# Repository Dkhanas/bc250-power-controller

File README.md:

# BC-250 power controller

A small board that gives an AMD BC-250 (running SteamOS) a real power button and Bluetooth controller wake-up.
A Raspberry Pi Pico 2 W sits on the ATX power supply's 5 V standby rail and:

- **Case button** short press: PSU on (the BC-250 auto-boots) / clean SteamOS shutdown (USB power key)
- **Case button held 5 s:** force the PSU off
- **Wi-Fi (optional):** a phone page / home-screen icon (`http://bc250.local`): power on, shut down, your controllers
  with battery, pair new ones, forget old ones. **Home Assistant** via MQTT (separate firmware file). Set up from your phone in a minute.
  Wi-Fi runs only when you want it: on request (default), only while the console is off, always, or never
- **Low-battery warning:** the controller rumbles and the button LED blinks when a DualSense / DualShock is at 20 % or less
- **Case button held 8 s (console off):** Wi-Fi on for the phone page
- **Case button held 2 s:** pairing window, which accepts a new controller for 60 s. Outside it, controllers in
  pairing mode are ignored, so you can still pair yours with a phone or PC
- **Bluetooth controller** (DualSense, DS4, Switch Pro, Xbox, 8BitDo…): pressing PS / Xbox / Home wakes the board,
  and the controller is passed to the BC-250 over USB (as itself, or as an Xbox 360 pad)
- **TPM pin 9** of the BC-250 goes low after shutdown -> PSU off after 5 s
- **Button LED:** slow blink booting, solid running, fast blink shutting down
- **Second fan** powered from the PSU's 12 V, speed controlled by the BC-250 (J4003)

| Printed board (PCB v12) | Test board (perfboard) |
|---|---|
|  |  |

## Repository

| Folder | What |
|---|---|
| [`firmware/`](firmware/) | Pico 2 W firmware (C, Pico SDK 2.3.1 + Bluepad32). Ready-to-flash file in [`firmware/release/`](firmware/release/) |
| [`pcb/`](pcb/) | Printed board, v12: KiCad project, Gerbers for JLCPCB / PCBWay / Aisler, notes |
| [`perfboard/`](perfboard/) | Test board on a 70×90 mm perfboard: hole-by-hole map |
| [`.github/workflows/`](.github/workflows/) | Automatic firmware build on GitHub; a version tag (`v8`) publishes a Release with both `.uf2` files |
| [`docs/`](docs/) | Build plan (wiring to the BC-250, SteamOS settings, mounting) and [pin drawings](docs/pinout.md) of every connector |
| [`CHANGELOG.md`](CHANGELOG.md) | Release notes: what's new, fixed and known issues in each firmware and PCB version |
| [`bom.csv`](bom.csv) | Parts list for both boards (opens in Excel; GitHub shows it as a table) |

## Quick start

1. **Flash:** hold BOOTSEL on the Pico, plug it into a PC, copy `firmware/release/bc250_power_v8.uf2` onto the `RP2350` drive
   (or `bc250_power_v8_ha.uf2` if you use Home Assistant).
2. **BC-250:** AUTO_PWRON jumper on pins 1–2; SteamOS `HandlePowerKey=poweroff`.
3. **Wire** per [`docs/build-plan.md`](docs/build-plan.md) (Pico GP15 -> PSU, GP17 <- button, GP16 -> LED, GP2 <- TPM pin 9).
   Pin drawings of every connector (BC-250 J4003 / TPMS1, ATX, board headers, Pico): [`docs/pinout.md`](docs/pinout.md).
4. **Pair a controller:** hold the case button 2 s and release (LED double-blinks), then put the controller in
   pairing mode within 60 s. Pairing turns the BC-250 on if it was off (expected).
5. **Optional Wi-Fi:** console off, hold the case button **8 s** (LED stays lit), release. On your phone tap the
   Wi-Fi **`BC250-setup`**; the setup page opens by itself. Pick your network, type its password, done. Then open
   `http://bc250.local` and *Add to Home Screen*. Wi-Fi switches itself off when unused (Settings → "Wi-Fi is on").

## Downsides and known limitations

**Testing status**
- **Firmware v8 compiles cleanly but hasn't been tested on real hardware yet** (v4 and v5 ran on the real board).
  Its web page was tested in a browser against a simulated Pico.
- **Wi-Fi and Bluetooth share one radio chip.** If controllers lag with Wi-Fi "Always", use "Only while the console
  is off" (Settings). Home Assistant only sees the BC-250 while Wi-Fi is on. Wi-Fi is 2.4 GHz only and adds a little standby power. Until a network is saved (or when it
  stays unreachable), the Pico runs the open setup Wi-Fi `BC250-setup`; someone nearby could set it up first.
  `bc250.local` doesn't open on some Android phones: use the Pico's address from your router. Without a PIN (`pin 1234`), anyone on your
  network can use the web page's buttons.
- **Battery level only for DualSense / DualShock**; Xbox, Switch Pro and 8BitDo don't report it to the Pico.
  Its key guard works around a Bluepad32 behaviour: after one failed reconnect Bluepad32 deletes the controller's
  pairing key, which made controllers "search" forever until re-paired. The Bluetooth repair from v5 stays for
  real radio hangs. The log (`sudo cat /dev/ttyACM0`) shows which one happened.
- **Controllers paired before v6 aren't protected until their first successful connection with v6.** If one
  already lost its key, re-pair it once.
- **Bluetooth repair takes a moment:** when Bluetooth is stuck, the Pico notices within about 30 s and restarts
  only Bluetooth, which takes a few more seconds. Until then, PS doesn't reconnect.
- **The log port only exists while no controller is connected**, so controller identities stay exact.
- **PCB v12 was checked with KiCad DRC, not built yet.** Everything except the ATX header was tested on a built v8 board;
  v12's ATX pin order matches what was measured there with the real PSU cable.
  Check the first board with a multimeter before connecting the PSU (see [`pcb/README.md`](pcb/README.md)).
  Check the first board with a multimeter before connecting the PSU (see [`pcb/README.md`](pcb/README.md)).
- **The perfboard map (v16) has the ATX header mirrored.** Wire it by wire colour, not by the hole numbers.

**Controllers**
- **Whenever a controller joins or leaves, every controller drops for about 0.5 s.** The Pico re-plugs itself on USB
  with the new layout, and Steam may reassign player numbers.
- **Several real DualSense / DS4 / Switch Pro controllers inside one USB device is unusual.** Linux supports it,
  but Steam may show only one of them. Mixed groups fall back to Xbox 360 pads, which lose the touchpad, gyro,
  lightbar and adaptive triggers.
- **No audio:** the DualSense / DS4 headphone jack, speaker and mic aren't passed through.
- **Up to 4 controllers. Only Bluetooth ones work**: no wired controllers through the Pico, and no non-Bluetooth Xbox One pads.
- **New controllers only pair while the pairing window is open** (case button held 2 s). Bluetooth LE controllers
  already bonded to the Pico (e.g. Xbox) are still taken when put in pairing mode, because they reconnect the same way.
- **Pairing a controller turns the BC-250 on.** For 20 s after a shutdown, controllers that reconnect are ignored,
  so a quick press of PS right after power-off does nothing.

**Power and shutdown**
- **The shutdown key is a USB "Power" key.** SteamOS has to be set to `HandlePowerKey=poweroff`. Gaming mode or an
  inhibitor can swallow it; then press again, or hold 5 s.
- **Holding the button for 5 s cuts power hard,** with no clean shutdown, like pulling the plug.
- **A short press while the board is booting is ignored.**
- **"Off" is detected from TPM header pin 9.** If the board doesn't boot within 180 s, the PSU is switched off again.
- **When a controller identity is active, the power key needs a ~2 s USB re-plug first.** The controllers vanish from
  SteamOS at that moment, which doesn't matter because it's shutting down.

**Hardware**
- **The Pico is always powered from the PSU's 5 V standby rail,** with its Bluetooth radio on, so the PC draws a little more
  power while "off".
- **With a normal USB cable, a little standby power can leak into the switched-off BC-250** through the Pico's
  internal diode (its back-panel LEDs may glow faintly). The clean fix is a cable with the red 5 V wire cut, plus
  `USE_VBUS_SENSE 0` in `firmware/src/config.h`.
- **Specific to the BC-250 and an ATX PSU** (needs AUTO_PWRON, the TPM header and J4003). Other boards need new pin mapping and logic.
- **No Wi-Fi features** (no web page or remote power-on over the network).

## ⚠️ Safety notes

- **ATX header orientation:** the two pin rows are **5.5 mm apart** (PCB v1–v8 used 4.2 mm: never use them).
  With the latch facing the wall, **pin 1 is at the FRONT end** (KiCad's official footprint, measured on a built v8 board).
  PCB v10 / v11 had it mirrored (12 V on GND): never use them. Use **PCB v9 or v12**.
- **Pico VBUS (pin 40) stays unconnected** on the board. The USB cable's 5 V (red wire) can leak standby power into a
  switched-off BC-250; firmware v4 and later handle a normal cable (`USE_VBUS_SENSE 1`).

## Versions

| | Version | Date |
|---|---|---|
| Firmware | v8 – Wi-Fi phone page (setup from the phone, controller list, pairing, forget) + Home Assistant, low-battery warning, pairing window, key guard, Bluetooth repair, event log | 2026-11-06 |
| PCB | v12 – v9 ATX pin order (confirmed with the real PSU cable) + gaps between the front headers | 2026-11-06 |
| Perfboard map | v16 (ATX header mirrored – wire it by wire colour) | 2026-10-18 |

**Building:** `bash firmware/build.sh` (library versions pinned in `firmware/deps.env`), or download the `.uf2` from
GitHub (Actions / Releases).

**Release notes for every version:** [`CHANGELOG.md`](CHANGELOG.md). Technical details: [`firmware/README.md`](firmware/README.md), [`pcb/README.md`](pcb/README.md).

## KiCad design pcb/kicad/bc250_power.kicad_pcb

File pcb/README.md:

# Printed board – PCB v12

| | |
|---|---|
| **Top** (component side, rendered from the board file) | **Bottom** (seen from below) |
|  |  |

**Wiring diagram** (colour-coded nets, dashed = top layer):

## Files
| File | What |
|---|---|
| [`gerbers/bc250_power_gerbers_v12.zip`](gerbers/bc250_power_gerbers_v12.zip) | Upload this to the board maker |
| [`kicad/`](kicad/) | KiCad 7+ project (`bc250_power.kicad_pro` / `.kicad_pcb`), `gen_board.py` (generates the board), `check_board.py` (clearance / connectivity check), `render_board.py` (makes the images) |
| [`images/`](images/) | The pictures on this page |

**Never use PCB v1–v8, v10 or v11.** v1–v8: ATX rows 4.2 mm apart (the real header is 5.5 mm), no peg holes.
v10 / v11: ATX pin order mirrored (pin 1 at the back) – 12 V on GND.

- Board 57.5 × 72 mm, 2 layers, 1.6 mm. 4 × M3 holes (3.2 mm); three at 3.5 mm from the corners, the front-right one
  3.0 mm from the right edge and 2.5 mm from the front edge (clears J3).
- Grid: hole (col 6, row 1) at x 6.5, y −1.0 mm; 2.54 mm pitch. Derived from perfboard map v16.

## Ordering
Upload `gerbers/bc250_power_gerbers_v12.zip` to JLCPCB / PCBWay / Aisler: 2 layers, 1.6 mm, defaults for everything else.

## ATX header (Molex Mini-Fit Jr 5566-24A2)
Latch faces the wall, pins 13–24 on the wall side, **pin 1 at the FRONT end, pins 12 / 24 at the back**.
Rows 5.5 mm apart, 3.3 × 2.7 mm oval pads, 1.4 mm drills, two 3.0 mm holes for the snap-in pegs.
Matches KiCad's official footprint pin-for-pin and was **confirmed with the real PSU cable on a built v8 board** (whose own ATX footprint was wrong;
everything else on it worked): 5 V standby is on the
4th pin from the back in the Pico-side row.

| ATX pin | Position (counted from the back / honeycomb wall end) | Goes to |
|---|---|---|
| 9 5VSB (purple) | Pico-side row, 4th | col 18 → D1 anode → Pico VSYS |
| 10 +12V (yellow) | Pico-side row, 3rd | top layer, x 40.8 mm → row 26 → J3 pin 3 |
| 15 GND (black) | wall-side row, 10th (3rd from the front) | lane beside the wall row → J3 pin 4 → row 29 → J1 GND → Pico GND |
| 16 PS_ON (green) | wall-side row, 9th (4th from the front) | channel between the rows → Q1 collector |

All-black modular cables: check with a multimeter (black probe on the PSU case): only the 5VSB pin reads ~5 V while the PSU is off.

## v12 (6 Nov 2026)
- v9's ATX pin order (confirmed with the real PSU cable) with v11's spaced-out front headers.
- Front row (row 27), left to right: J1 button (cols 12–14: LED+, C, GND), gap, J2 TPM9 (col 16), gap,
  J4 → J4003 (cols 18 T, 19 P), gap, J3 fan 2 (cols 21–24: PWM, TACH, 12V, GND).
- Checks: KiCad DRC 0 electrical errors, 0 unconnected pads; independent clearance/connectivity script 0 errors;
  ATX pads compared with the official footprint (0.0 mm error).

## Layout
- Q1 2N2222 flat on row 3 (E col 15, B col 16, C col 17). R1 1k row 5 (col 14 → 17). R2 10k col 16 (row 6 base → row 9 GND).
  v12 moved Q1 and R2 left: ≥ 5.5 mm between them and the ATX connector body (was 0.4 mm).
- R3 220 Ω col 15 (rows 21–24) → J2. D1 1N5819 row 25 (K col 14, A col 18), VSYS row 25 → col 7 → Pico pin 39.
- Pico on cols 6/13 rows 5–24; VBUS (pin 40) unconnected.
- Trace widths: 1.0 mm for GND / 5VSB / VSYS / 12V, 0.4–0.6 mm for signals.

## Before first power-up
Plug the PSU cable in (PSU off): pad 9 must read +5 V to GND, every other ATX pad 0 V.
Then Pico VSYS (2nd pin from the USB end, left row) ≈ 4.7 V and 3V3 (5th pin) = 3.3 V.

## History
- v2–v5 (18 Oct): narrower board, J1 to the front, headers in one row, J2 joins the row.
- v6–v8: layout tweaks. v8 was built: everything worked except the ATX header (4.2 mm rows, mirrored).
- v9 (19 Oct): ATX header corrected (5.5 mm rows, peg holes, pin 1 at the front). Pin order later confirmed with the real PSU cable.
- v10 / v11 (6 Nov): pin 1 at the back + gaps between front headers – **wrong pin order, do not use**.
- v12 (6 Nov): v9 pin order + v11 gaps.

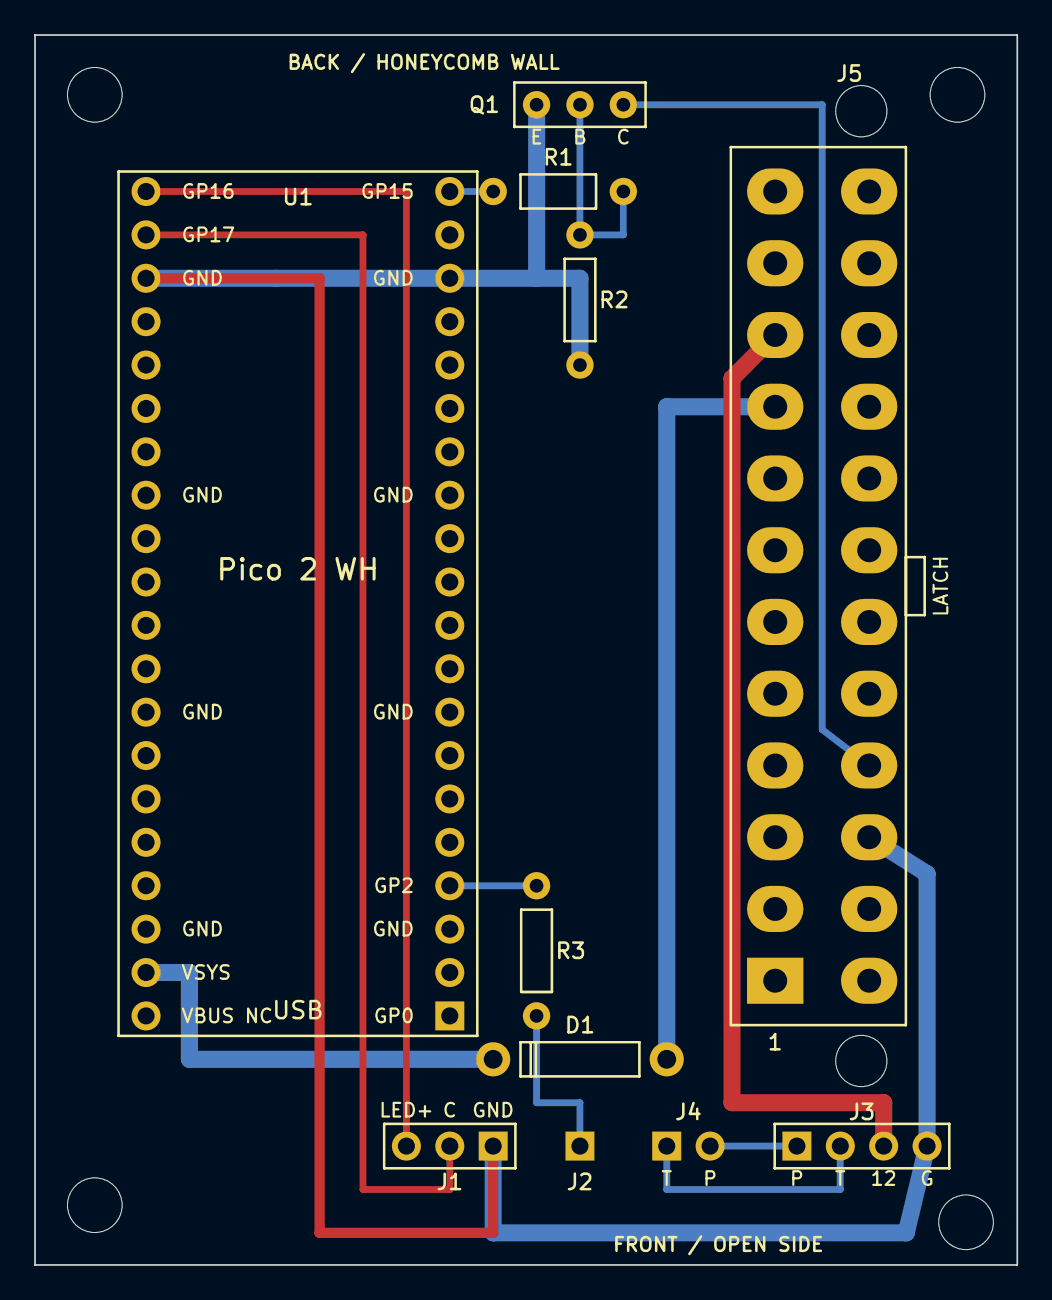
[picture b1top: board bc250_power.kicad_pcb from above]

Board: 2 copper layers, 57.5 x 72.0 mm, 15 parts (0 on the bottom side), 13 nets.

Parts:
D1: 1N5819; D1_1N5819
H1: M3; H1_M3
H2: M3; H2_M3
H3: M3; H3_M3
H4: M3; H4_M3
J1: BUTTON; J1_BUTTON
J2: TPM9; J2_TPM9
J3: FAN2; J3_FAN2
J4: J4003; J4_J4003
J5: ATX24; J5_ATX24
Q1: 2N2222; Q1_2N2222
R1: 1k; R1_1k
R2: 10k; R2_10k
R3: 220R; R3_220R
U1: Pico2WH; U1_Pico2WH

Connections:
5VSB: D1.A, J5.9
+12V: J3.3, J5.10
BTN: J1.2, U1.22
FAN_PWM: J3.1, J4.2
FAN_TACH: J3.2, J4.1
GND: J1.1, J3.4, J5.15, Q1.E, R2.2, U1.18, U1.23
GP2: R3.1, U1.4
GP15: R1.1, U1.20
LED+: J1.3, U1.21
PS_ON: J5.16, Q1.C
Q1_BASE: Q1.B, R1.2, R2.1
TPM9: J2.1, R3.2
VSYS: D1.K, U1.39
